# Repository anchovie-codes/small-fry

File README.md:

# small-fry

rev. 1 prototype

## parts needed

- 1x Raspberry Pi Pico (make sure you get an [authentic one](https://www.raspberrypi.com/products/raspberry-pi-pico/) with the castellated pins)
- 69x SOD123 diodes (e.g. [1N4148W](https://www.digikey.com/en/products/detail/micro-commercial-co/1N4148W-TP/717196))
- 69 MX or Alps switches (i **strongly recommend MX** unless you are confident in fabricating your own keycaps)
- 2x 2U stabilizers
- 53x 1U keycaps
- 14x 1.75U keycaps
- 1x 2.25U keycap
- 1x 2.75U keycap

## tools needed

- **a heat gun + solder paste are highly recommended** for soldering the diodes, however they can be hand-soldered if you are patient and skilled.
- soldering iron + solder  wire for soldering the switches and MCU.

## assembly notes

- diode direction is COL to ROW! this means the lines should face down (if you're using the diodes linked above).
- this PCB does not have holes for tray-mounting; it must be plate-mounted to a case.
- switchplate .DXF file is included; it should be ~1.5mm thick. recommended material is either metal or FR4. acrylic is technically viable but will add flex.

### sandwich case notes

some .DXF files are included for a rudimentary sandwich case. additional hardware needed:
- 10x M3x8mm male-to-female standoffs (M3x10 will also work, just makes the height taller)
- 10x M3x4mm screws
- 10x M3x6x5mm heat-threaded inserts

required thickness of each plate:
- top plate: 1.5-3mm
- mid plate: 3mm
- buffer plate: 3mm
- bottom plate: 1.5-3mm

stacking order of plates is, from top to bottom:
- top plate
- mid plate
- buffer plate
- switch plate
- bottom plate

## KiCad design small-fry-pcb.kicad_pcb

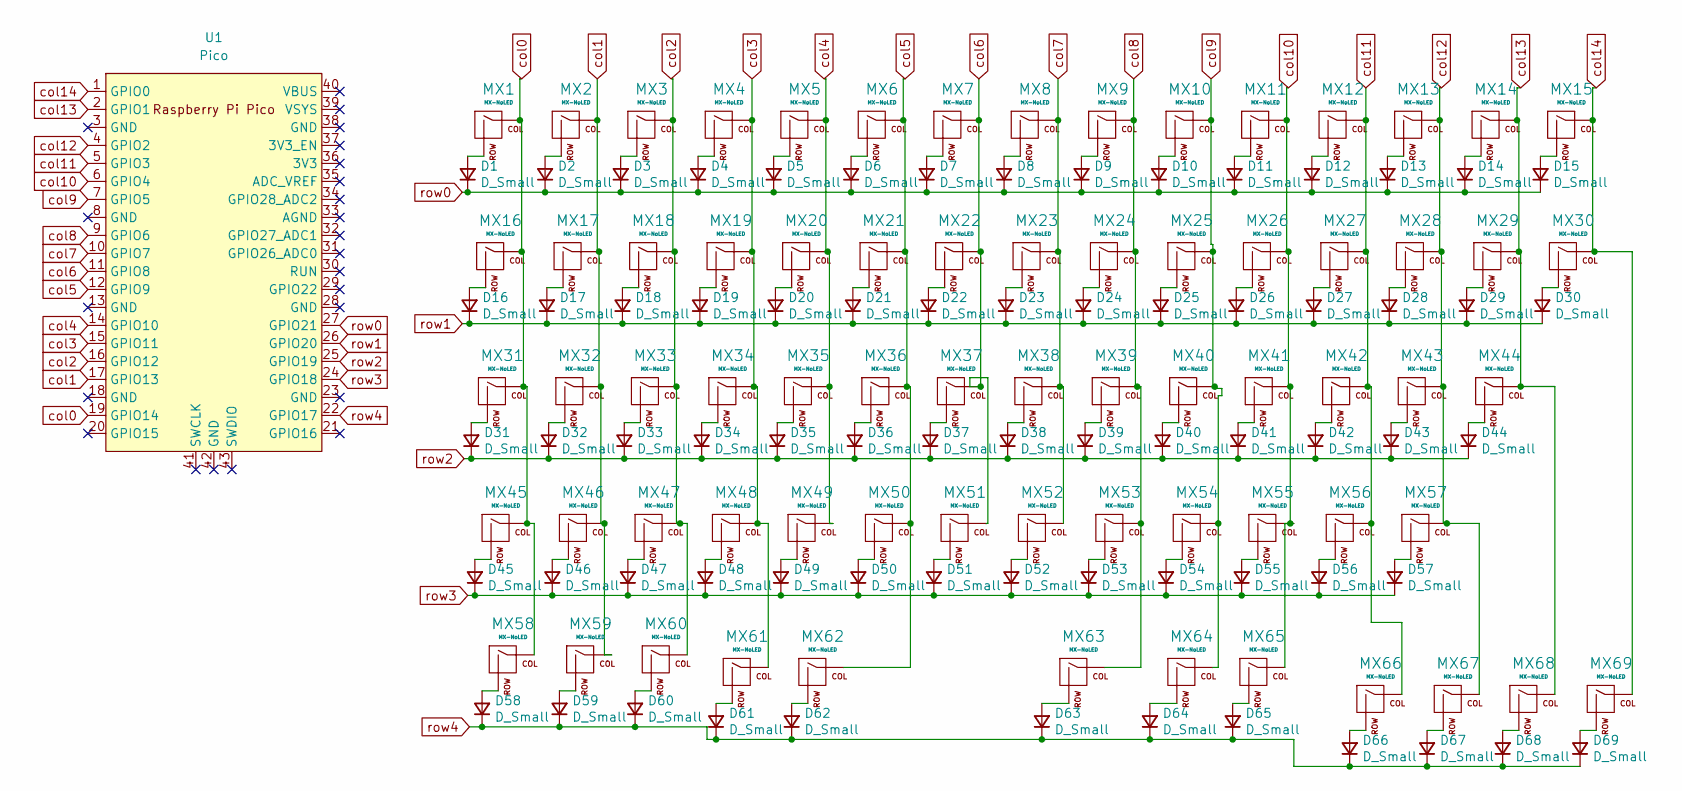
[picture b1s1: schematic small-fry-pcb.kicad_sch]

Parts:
D1, D2, D3, D4, D5, D6, D7, D8, D9, D10, D11, D12, D13, D14, D15, D16, D17, D18, D19, D20, D21, D22, D23, D24, D25, D26, D27, D28, D29, D30, D31, D32, D33, D34, D35, D36, D37, D38, D39, D40, D41, D42, D43, D44, D45, D46, D47, D48, D49, D50, D51, D52, D53, D54, D55, D56, D57, D58, D59, D60, D61, D62, D63, D64, D65, D66, D67, D68, D69: D_Small; D_SOD-123
MX1, MX16, MX31, MX45, MX58: MX-NoLED; SW_MX_1.25u
MX2, MX15, MX17, MX30, MX32, MX44, MX46, MX57, MX59: MX-NoLED; SW_MX_1.5u
MX3, MX4, MX5, MX6, MX7, MX8, MX9, MX10, MX11, MX12, MX13, MX14, MX18, MX19, MX20, MX21, MX22, MX23, MX24, MX25, MX26, MX27, MX28, MX29, MX33, MX34, MX35, MX36, MX37, MX38, MX39, MX40, MX41, MX42, MX43, MX47, MX48, MX49, MX50, MX51, MX52, MX53, MX54, MX55, MX56, MX60, MX61, MX64, MX65, MX66, MX67, MX68, MX69: MX-NoLED; SW_MX_1u
MX62: MX-NoLED; MX-Solderable-2.25U-ReversedStabilizers
MX63: MX-NoLED; MX-Solderable-2.75U-ReversedStabilizers
U1: Pico; RPi_Pico_SMD_TH

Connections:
unnamed: D1.2 (A), MX1.2 (ROW)
unnamed: D2.2 (A), MX2.2 (ROW)
unnamed: D3.2 (A), MX3.2 (ROW)
unnamed: D4.2 (A), MX4.2 (ROW)
unnamed: D5.2 (A), MX5.2 (ROW)
unnamed: D6.2 (A), MX6.2 (ROW)
unnamed: D7.2 (A), MX7.2 (ROW)
unnamed: D8.2 (A), MX8.2 (ROW)
unnamed: D9.2 (A), MX9.2 (ROW)
unnamed: D10.2 (A), MX10.2 (ROW)
unnamed: D11.2 (A), MX11.2 (ROW)
unnamed: D12.2 (A), MX12.2 (ROW)
unnamed: D13.2 (A), MX13.2 (ROW)
unnamed: D14.2 (A), MX14.2 (ROW)
unnamed: D15.2 (A), MX15.2 (ROW)
unnamed: D16.2 (A), MX16.2 (ROW)
unnamed: D17.2 (A), MX17.2 (ROW)
unnamed: D18.2 (A), MX18.2 (ROW)
unnamed: D19.2 (A), MX19.2 (ROW)
unnamed: D20.2 (A), MX20.2 (ROW)
unnamed: D21.2 (A), MX21.2 (ROW)
unnamed: D22.2 (A), MX22.2 (ROW)
unnamed: D23.2 (A), MX23.2 (ROW)
unnamed: D24.2 (A), MX24.2 (ROW)
unnamed: D25.2 (A), MX25.2 (ROW)
unnamed: D26.2 (A), MX26.2 (ROW)
unnamed: D27.2 (A), MX27.2 (ROW)
unnamed: D28.2 (A), MX28.2 (ROW)
unnamed: D29.2 (A), MX29.2 (ROW)
unnamed: D30.2 (A), MX30.2 (ROW)
unnamed: D31.2 (A), MX31.2 (ROW)
unnamed: D32.2 (A), MX32.2 (ROW)
unnamed: D33.2 (A), MX33.2 (ROW)
unnamed: D34.2 (A), MX34.2 (ROW)
unnamed: D35.2 (A), MX35.2 (ROW)
unnamed: D36.2 (A), MX36.2 (ROW)
unnamed: D37.2 (A), MX37.2 (ROW)
unnamed: D38.2 (A), MX38.2 (ROW)
unnamed: D39.2 (A), MX39.2 (ROW)
unnamed: D40.2 (A), MX40.2 (ROW)
unnamed: D41.2 (A), MX41.2 (ROW)
unnamed: D42.2 (A), MX42.2 (ROW)
unnamed: D43.2 (A), MX43.2 (ROW)
unnamed: D44.2 (A), MX44.2 (ROW)
unnamed: D45.2 (A), MX45.2 (ROW)
unnamed: D46.2 (A), MX46.2 (ROW)
unnamed: D47.2 (A), MX47.2 (ROW)
unnamed: D48.2 (A), MX48.2 (ROW)
unnamed: D49.2 (A), MX49.2 (ROW)
unnamed: D50.2 (A), MX50.2 (ROW)
unnamed: D51.2 (A), MX51.2 (ROW)
unnamed: D52.2 (A), MX52.2 (ROW)
unnamed: D53.2 (A), MX53.2 (ROW)
unnamed: D54.2 (A), MX54.2 (ROW)
unnamed: D55.2 (A), MX55.2 (ROW)
unnamed: D56.2 (A), MX56.2 (ROW)
unnamed: D57.2 (A), MX57.2 (ROW)
unnamed: D58.2 (A), MX58.2 (ROW)
unnamed: D59.2 (A), MX59.2 (ROW)
unnamed: D60.2 (A), MX60.2 (ROW)
unnamed: D61.2 (A), MX61.2 (ROW)
unnamed: D62.2 (A), MX62.2 (ROW)
unnamed: D63.2 (A), MX63.2 (ROW)
unnamed: D64.2 (A), MX64.2 (ROW)
unnamed: D65.2 (A), MX65.2 (ROW)
unnamed: D66.2 (A), MX66.2 (ROW)
unnamed: D67.2 (A), MX67.2 (ROW)
unnamed: D68.2 (A), MX68.2 (ROW)
unnamed: D69.2 (A), MX69.2 (ROW)
col0: MX1.1 (COL), MX16.1 (COL), MX31.1 (COL), MX45.1 (COL), MX58.1 (COL), U1.19 (GPIO14)
col1: MX2.1 (COL), MX17.1 (COL), MX32.1 (COL), MX46.1 (COL), MX59.1 (COL), U1.17 (GPIO13)
col2: MX3.1 (COL), MX18.1 (COL), MX33.1 (COL), MX47.1 (COL), MX60.1 (COL), U1.16 (GPIO12)
col3: MX4.1 (COL), MX19.1 (COL), MX34.1 (COL), MX48.1 (COL), MX61.1 (COL), U1.15 (GPIO11)
col4: MX5.1 (COL), MX20.1 (COL), MX35.1 (COL), MX49.1 (COL), U1.14 (GPIO10)
col5: MX6.1 (COL), MX21.1 (COL), MX36.1 (COL), MX50.1 (COL), MX62.1 (COL), U1.12 (GPIO9)
col6: MX7.1 (COL), MX22.1 (COL), MX37.1 (COL), MX51.1 (COL), U1.11 (GPIO8)
col7: MX8.1 (COL), MX23.1 (COL), MX38.1 (COL), MX52.1 (COL), U1.10 (GPIO7)
col8: MX9.1 (COL), MX24.1 (COL), MX39.1 (COL), MX53.1 (COL), MX63.1 (COL), U1.9 (GPIO6)
col9: MX10.1 (COL), MX25.1 (COL), MX40.1 (COL), MX54.1 (COL), MX64.1 (COL), U1.7 (GPIO5)
col10: MX11.1 (COL), MX26.1 (COL), MX41.1 (COL), MX55.1 (COL), MX65.1 (COL), U1.6 (GPIO4)
col11: MX12.1 (COL), MX27.1 (COL), MX42.1 (COL), MX56.1 (COL), MX66.1 (COL), U1.5 (GPIO3)
col12: MX13.1 (COL), MX28.1 (COL), MX43.1 (COL), MX57.1 (COL), MX67.1 (COL), U1.4 (GPIO2)
col13: MX14.1 (COL), MX29.1 (COL), MX44.1 (COL), MX68.1 (COL), U1.2 (GPIO1)
col14: MX15.1 (COL), MX30.1 (COL), MX69.1 (COL), U1.1 (GPIO0)
row0: D1.1 (K), D2.1 (K), D3.1 (K), D4.1 (K), D5.1 (K), D6.1 (K), D7.1 (K), D8.1 (K), D9.1 (K), D10.1 (K), D11.1 (K), D12.1 (K), D13.1 (K), D14.1 (K), D15.1 (K), U1.27 (GPIO21)
row1: D16.1 (K), D17.1 (K), D18.1 (K), D19.1 (K), D20.1 (K), D21.1 (K), D22.1 (K), D23.1 (K), D24.1 (K), D25.1 (K), D26.1 (K), D27.1 (K), D28.1 (K), D29.1 (K), D30.1 (K), U1.26 (GPIO20)
row2: D31.1 (K), D32.1 (K), D33.1 (K), D34.1 (K), D35.1 (K), D36.1 (K), D37.1 (K), D38.1 (K), D39.1 (K), D40.1 (K), D41.1 (K), D42.1 (K), D43.1 (K), D44.1 (K), U1.25 (GPIO19)
row3: D45.1 (K), D46.1 (K), D47.1 (K), D48.1 (K), D49.1 (K), D50.1 (K), D51.1 (K), D52.1 (K), D53.1 (K), D54.1 (K), D55.1 (K), D56.1 (K), D57.1 (K), U1.24 (GPIO18)
row4: D58.1 (K), D59.1 (K), D60.1 (K), D61.1 (K), D62.1 (K), D63.1 (K), D64.1 (K), D65.1 (K), D66.1 (K), D67.1 (K), D68.1 (K), D69.1 (K), U1.22 (GPIO17)

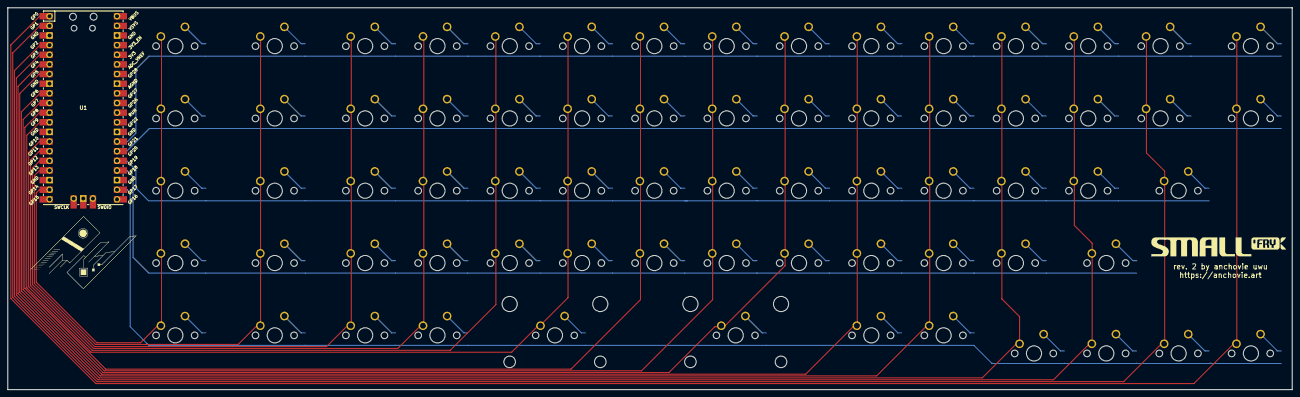
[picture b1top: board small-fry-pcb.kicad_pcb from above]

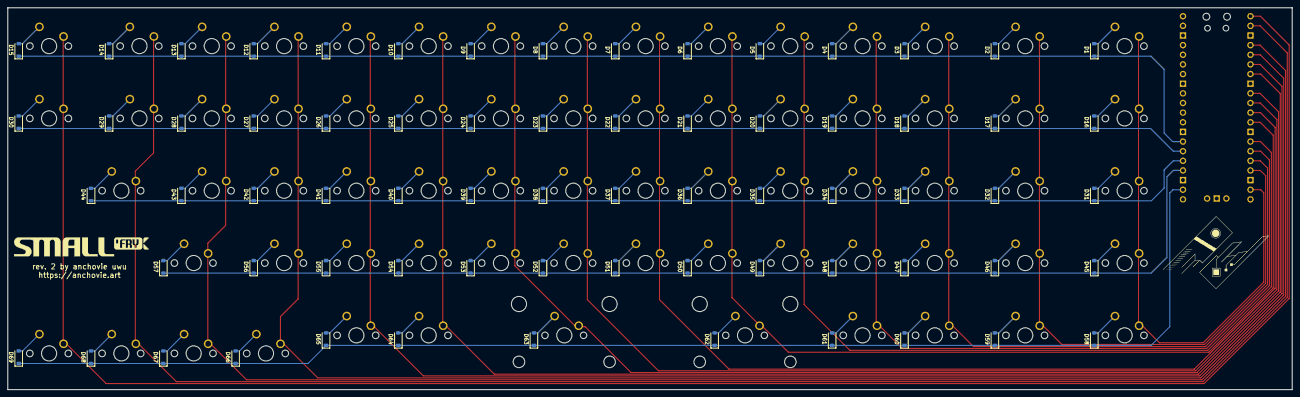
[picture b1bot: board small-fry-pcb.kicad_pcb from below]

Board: 2 copper layers, 338.4 x 100.6 mm, 139 parts (69 on the bottom side), 89 nets.

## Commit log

2024-08-31 added kicad files
2024-08-31 added libraries
2024-08-31 updated schematic
2024-08-31 updated schematic and fixed footprints
2024-09-01 added controller footprint and symbol
2024-09-04 Squashed commit of the following:
    commit 3a31e5c864698379eab5fa9799b6646026e60a6b
    Author: anchovie-codes <littlebrother.free@gmail.com>
    Date: Mon Sep 2 00:25:19 2024 -0400
    backup file changes
    commit 27ca4d82953605882c5c8308233a3a86d2bdc34d
    Author: anchovie-codes <littlebrother.free@gmail.com>
2024-09-04 updated matrix routing
2024-09-04 adjusted col traces and silkscreen
2024-09-04 updated backup
2024-09-04 Squashed commit of the following:
    commit 176f3bbe4c1d8503f8e6634e84449ff57851d2da
    Author: anchovie-codes <littlebrother.free@gmail.com>
    Date: Wed Sep 4 12:11:39 2024 -0400
    updated backup
    commit faa0e4d37d006ebb0d8ebb4d260e99f9d3fc7be4
    Author: anchovie-codes <littlebrother.free@gmail.com>
2024-09-04 added extra switches
    to accommodate the switch holes, leftmost diodes were moved and col routing was modified. extra pads connect back to the diodes.
2024-09-05 generated gerbers
2024-09-06 added firmware reference files
2024-09-06 updated firmware with keymap and vial support
2024-09-11 added vial rules.mk
2024-09-11 changed info.json to keyboard.json
2024-09-11 duped keymap.c to vial
2024-09-11 commented out broken config.h lines
2024-09-11 undid all the stupid renaming
2024-09-11 fixed super swap keybinds
2024-09-11 removed macros for testing purposes
2024-09-11 removed macros, fixed keymap in vial
2024-09-11 renamed info.json
2024-09-11 added default compiled firmware
2024-09-11 added M1 as test
2024-09-14 updated keymap files
2024-09-16 pcb backup updates
2024-09-17 changed mods, changed col stagger
2024-09-18 fixed layer 2 toggle, added mousekeys
2024-09-27 changed footprints, rerouted
